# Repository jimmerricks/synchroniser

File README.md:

# Synchroniser

This Eurorack module is a hand-solderable 4hp version of [Hagiwo's Clock Sync LFO](https://note.com/solder_state/n/n4c600f2431c3). It is based on [the schematics and design by mzuelch](https://github.com/mzuelch/CATs-Eurosynth/tree/main/Modules/HAGIWO/Sync%20LFO) but adds a couple of buttons and an extra LED. It is Arduino Nano based and compatible with firmware released by [mzuelch](https://github.com/mzuelch/CATs-Eurosynth/tree/main/Modules/HAGIWO/Sync%20LFO/Firmware), [awonak](https://awonak.github.io/HagiwoModulove/synclfo/) and [Modulove](https://dl.modulove.de/module/synclfo/).

## BOM

Use the [ibom](https://htmlpreview.github.io/?https://github.com/jimmerricks/synchroniser/blob/main/bom/ibom.html) to assist with sourcing components, and as a placement guide when building the module.

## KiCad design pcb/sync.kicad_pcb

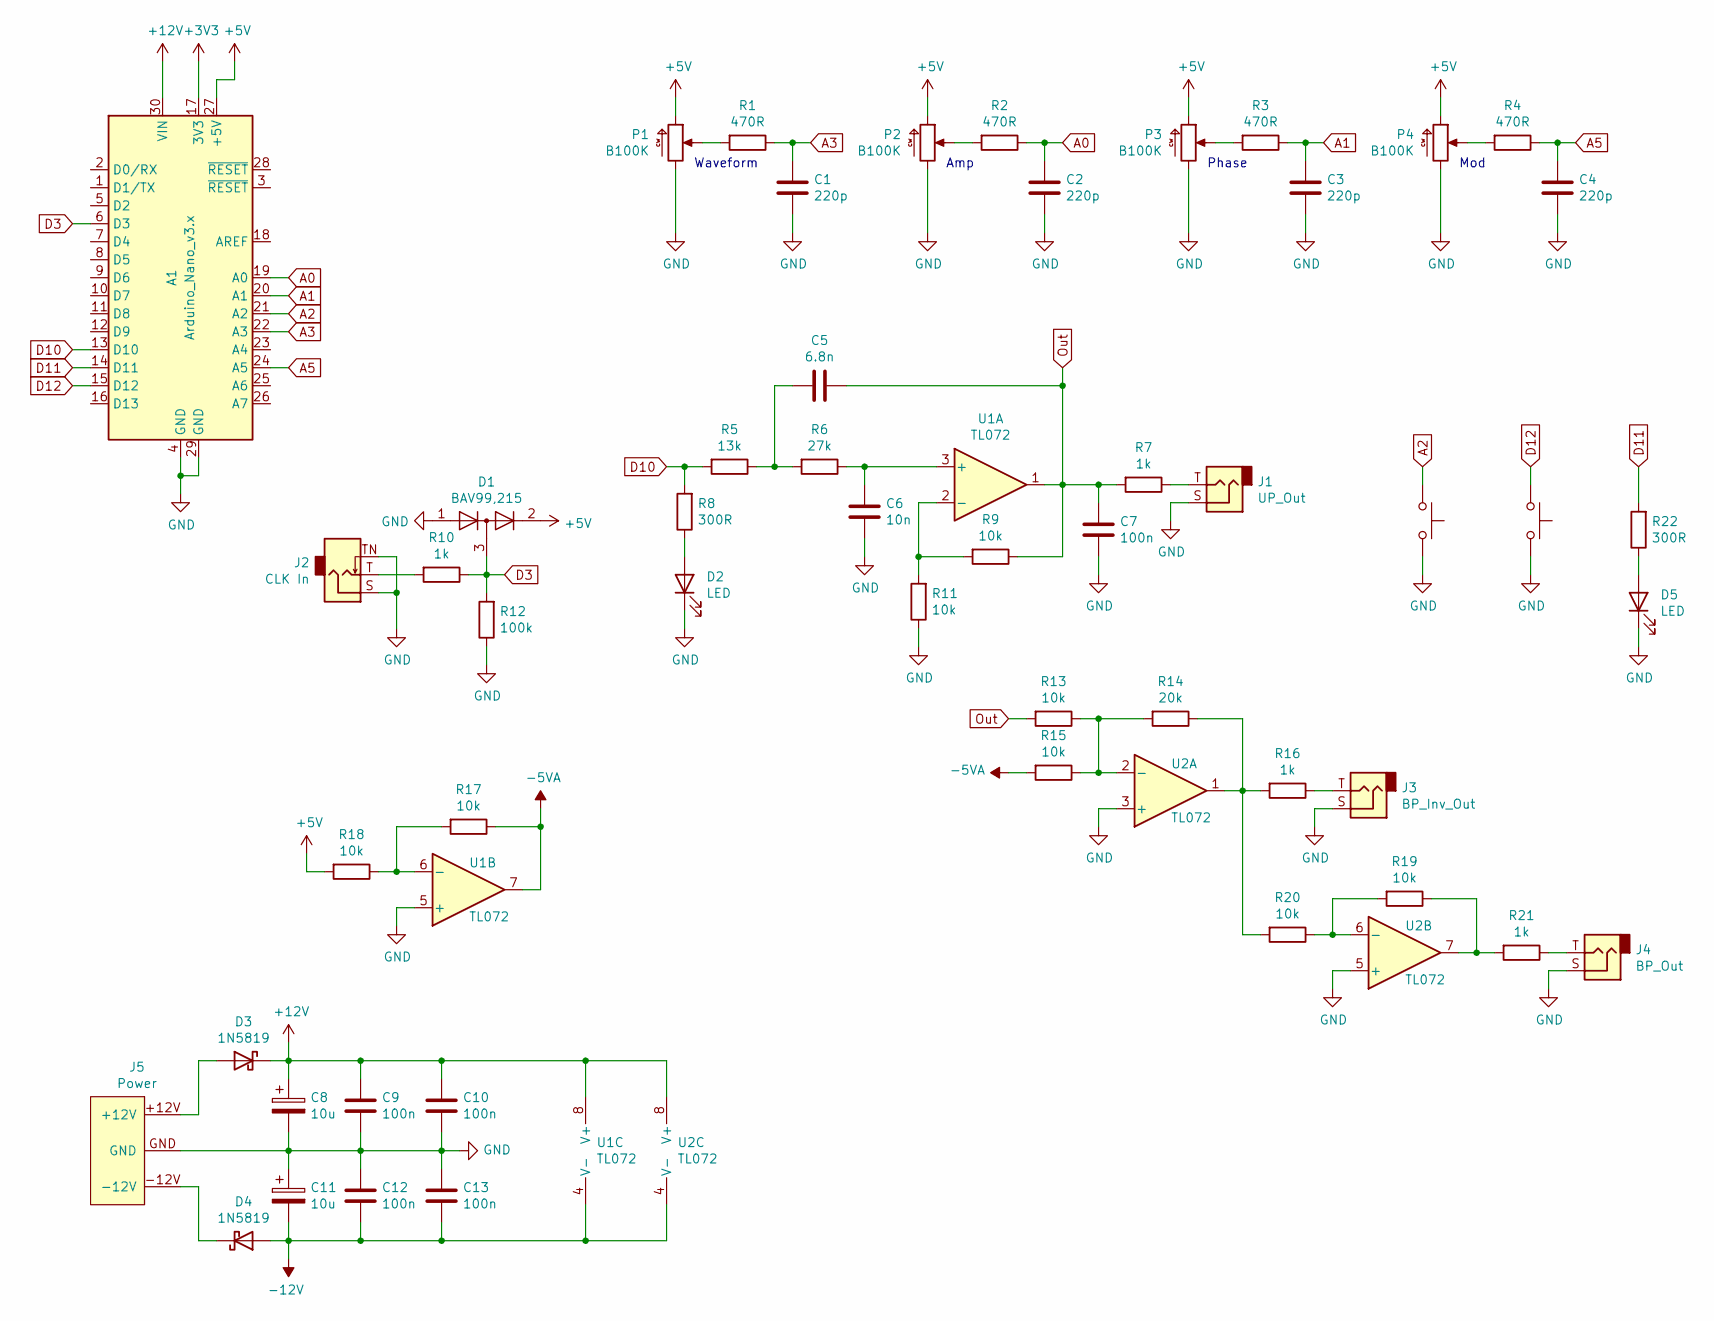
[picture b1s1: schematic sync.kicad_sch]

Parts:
A1: Arduino_Nano_v3.x; Arduino_Nano
C1, C2, C3, C4: 220p; C_0402_1005Metric; LCSC C1530
C5: 6.8n; C_0402_1005Metric; LCSC C1542
C6: 10n; C_0402_1005Metric; LCSC C15195
C7, C9, C10, C12, C13: 100n; C_0402_1005Metric; LCSC C1525
C8, C11: 10u; CP_EIA-3216-18_Kemet-A; LCSC C7171
D1: BAV99,215; SOT-23; LCSC C2500
D2, D5: LED; LED_D3.0mm
D3, D4: 1N5819; D_SOD-323; LCSC C191023
J1: UP_Out; Jack_3.5mm_QingPu_WQP-PJ301M-12
J2: CLK In; Jack_3.5mm_QingPu_WQP-PJ301M-12
J3: BP_Inv_Out; Jack_3.5mm_QingPu_WQP-PJ301M-12
J4: BP_Out; Jack_3.5mm_QingPu_WQP-PJ301M-12
J5: Power; Power_2x5_Vertical
P1, P3, P4: B100K; Potentiometer_AlpsAlpine_RK09L1140_wo_Fix
P2: B100K; Potentiometer_AlpsAlpine_RK09L1140
R1, R2, R3, R4: 470R; R_0402_1005Metric; LCSC C25117
R5: 13k; R_0603_1608Metric; LCSC C22797
R6: 27k; R_0402_1005Metric; LCSC C25771
R7, R10, R16, R21: 1k; R_0402_1005Metric; LCSC C11702
R8, R22: 300R; R_0402_1005Metric; LCSC C25102
R9, R11, R13, R15, R17, R18, R19, R20: 10k; R_0402_1005Metric; LCSC C25744
R12: 100k; R_0402_1005Metric; LCSC C25741
R14: 20k; R_0402_1005Metric; LCSC C25765
SW1, SW2: Button; SW_PUSH_6mm
U1, U2: TL072; SOIC-8_3.9x4.9mm_P1.27mm; LCSC C6961

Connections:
+3V3: A1.17 (3V3)
+5V: A1.27 (+5V), D1.2 (A), P1.CW, P2.CW, P3.CW, P4.CW, R18.2
+12V: A1.30 (VIN), C8.1, C9.2, C10.2, D3.1 (K), U1.8 (V+), U2.8 (V+)
-5VA: R15.2, R17.1, U1.7
-12V: C11.2, C12.1, C13.1, D4.2 (A), U1.4 (V-), U2.4 (V-)
A0: A1.19 (A0), C2.1, R2.1
A1: A1.20 (A1), C3.1, R3.1
A2: A1.21 (A2), SW1.1
A3: A1.22 (A3), C1.1, R1.1
A5: A1.24 (A5), C4.1, R4.1
D3: A1.6 (D3), D1.3 (K), R10.1, R12.2
D10: A1.13 (D10), R5.2, R8.2
D11: A1.14 (D11), R22.2
D12: A1.15 (D12), SW2.1
GND: A1.4 (GND), A1.29 (GND), C1.2, C2.2, C3.2, C4.2, C6.1, C7.1, C8.2, C9.1, C10.1, C11.1, C12.2, C13.2, D1.1 (K), D2.1 (K), D5.1 (K), J1.S, J2.S, J2.TN, J3.S, J4.S, J5.GND, P1.CCW, P2.CCW, P3.CCW, P4.CCW, R11.1, R12.1, SW1.2, SW2.2, U1.5 (+), U2.3 (+), U2.5 (+)
unnamed: C5.2, R5.1, R6.2
unnamed: D2.2 (A), R8.1
unnamed: D3.2 (A), J5.+12V
unnamed: D4.1 (K), J5.-12V
unnamed: D5.2 (A), R22.1
unnamed: J1.T, R7.1
unnamed: J2.T, R10.2
unnamed: J3.T, R16.1
unnamed: J4.T, R21.1
unnamed: P1.W, R1.2
unnamed: P2.W, R2.2
unnamed: P3.W, R3.2
unnamed: P4.W, R4.2
unnamed: R14.1, R16.2, R20.2, U2.1
unnamed: R19.1, R21.2, U2.7
unnamed: C6.2, R6.1, U1.3 (+)
unnamed: R9.2, R11.2, U1.2 (-)
unnamed: R17.2, R18.1, U1.6 (-)
unnamed: R13.1, R14.2, R15.1, U2.2 (-)
unnamed: R19.2, R20.1, U2.6 (-)
Out: C5.1, C7.2, R7.2, R9.1, R13.2, U1.1

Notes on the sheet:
Amp
Waveform
Phase
Mod

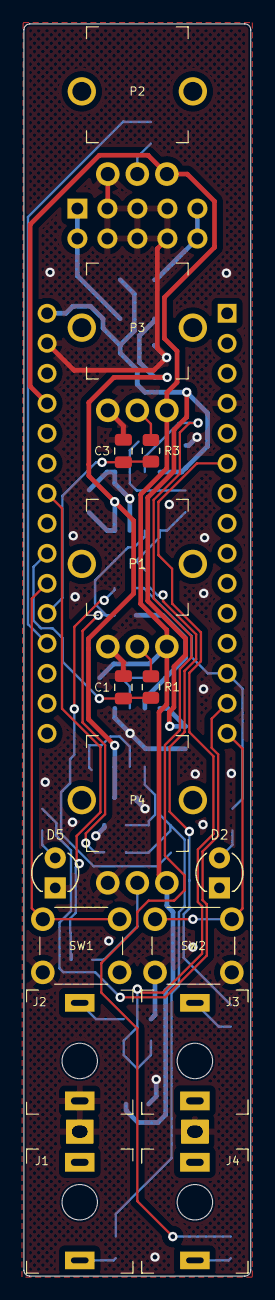
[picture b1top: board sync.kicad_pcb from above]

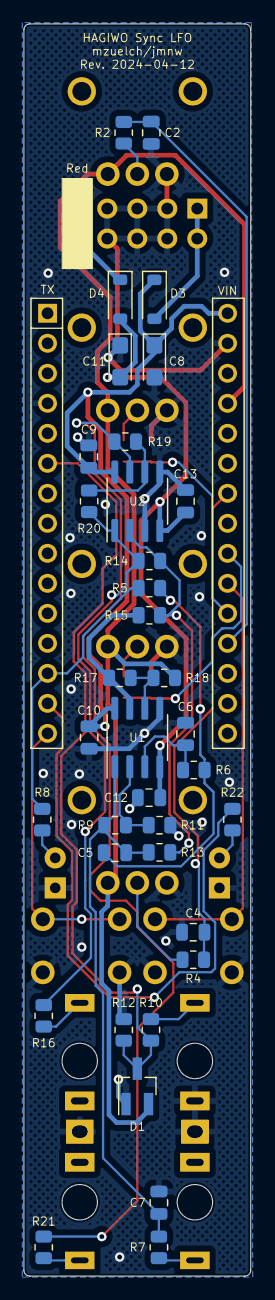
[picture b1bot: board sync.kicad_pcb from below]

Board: 2 copper layers, 19.2 x 106.0 mm, 54 parts (38 on the bottom side), 35 nets.

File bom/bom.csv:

Id,Designator,Footprint,Quantity,Designation,Reference
1,"C1,C3,C2,C4",C_0805_2012Metric,4,220p,GCM2165C1H221JA16D
2,"D2,D5",LED_D3.0mm,2,LED,WP710A10ED
3,J3,Jack_3.5mm_QingPu_WQP-PJ301M-12,1,BP_Inv_Out,eg. Thonk
4,J4,Jack_3.5mm_QingPu_WQP-PJ301M-12,1,BP_Out,
5,"P1,P3,P4",Potentiometer_AlpsAlpine_RK09L1140_wo_Fix,3,B100K,eg. Thonk
6,P2,Potentiometer_AlpsAlpine_RK09L1140,1,B100K,
7,"R3,R1,R2,R4",R_0805_2012Metric,4,470R,RC0805FR-07470RL
8,J2,Jack_3.5mm_QingPu_WQP-PJ301M-12,1,CLK In,
9,J1,Jack_3.5mm_QingPu_WQP-PJ301M-12,1,UP_Out,
10,"SW1,SW2",SW_PUSH_6mm,2,Button,TL1105SPF100Q (cap: 1RBLK)
11,A1,Arduino_Nano,1,Arduino_Nano_v3.x,eg. AliExpress (sockets: 90147-1115)
12,C5,C_0805_2012Metric,1,6.8n,GRM2195C1H682JA01J
13,C6,C_0805_2012Metric,1,10n,GCM216R71H103JA37D
14,"C7,C9,C10,C12,C13",C_0805_2012Metric,5,100n,GCM21BR71H104JA37L
15,"C8,C11",CP_EIA-3216-18_Kemet-A,2,10u,C1206C106J3RACAUTO
16,D1,SOT-23_Handsoldering,1,"BAV99,215","BAV99,215"
17,"D3,D4",D_SOD-123,2,1N5819,1N5819HW-7-F
18,J5,Power_2x5_Vertical,1,Power,90131-1085
19,R5,R_0805_2012Metric,1,13k,RC0805FR-0713KL
20,R6,R_0805_2012Metric,1,27k,RC0805FR-0727KL
21,"R7,R10,R16,R21",R_0805_2012Metric,4,1k,RC0805FR-071KL
22,"R8,R22",R_0805_2012Metric,2,300R,RC0805FR-07300RL
23,"R9,R13,R15,R17,R18,R19,R20,R11",R_0805_2012Metric,8,10k,RC0805FR-0710KL
24,R12,R_0805_2012Metric,1,100k,RC0805FR-07100KL
25,R14,R_0805_2012Metric,1,20k,RC0805FR-0720KL
26,"U1,U2",SOIC-8_3.9x4.9mm_P1.27mm,2,TL072,TL072CDR

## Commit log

2024-04-12 Revised PCB files with the button connected to A2.
2024-04-12 Basic 3u panel for printing or cutting.
2024-04-12 BOM in both CSV and HTML versions.
2024-04-12 Basic README with links to firmware.
2024-04-16 Update README.md
    Minor nitpick suggestions for links and attribution.
2024-04-16 Add bom link
2024-04-26 Add 1u panel svg
